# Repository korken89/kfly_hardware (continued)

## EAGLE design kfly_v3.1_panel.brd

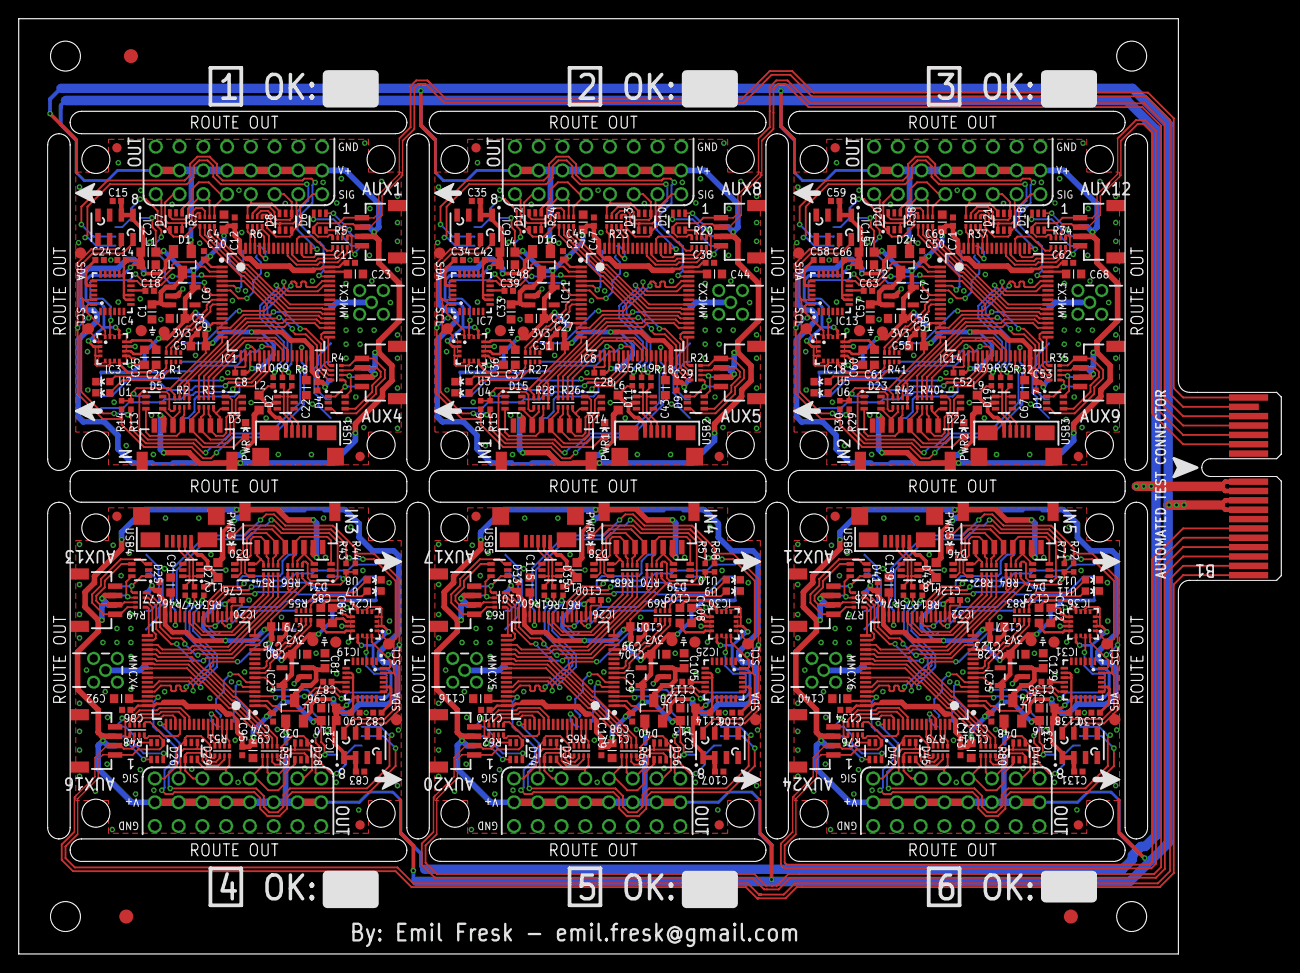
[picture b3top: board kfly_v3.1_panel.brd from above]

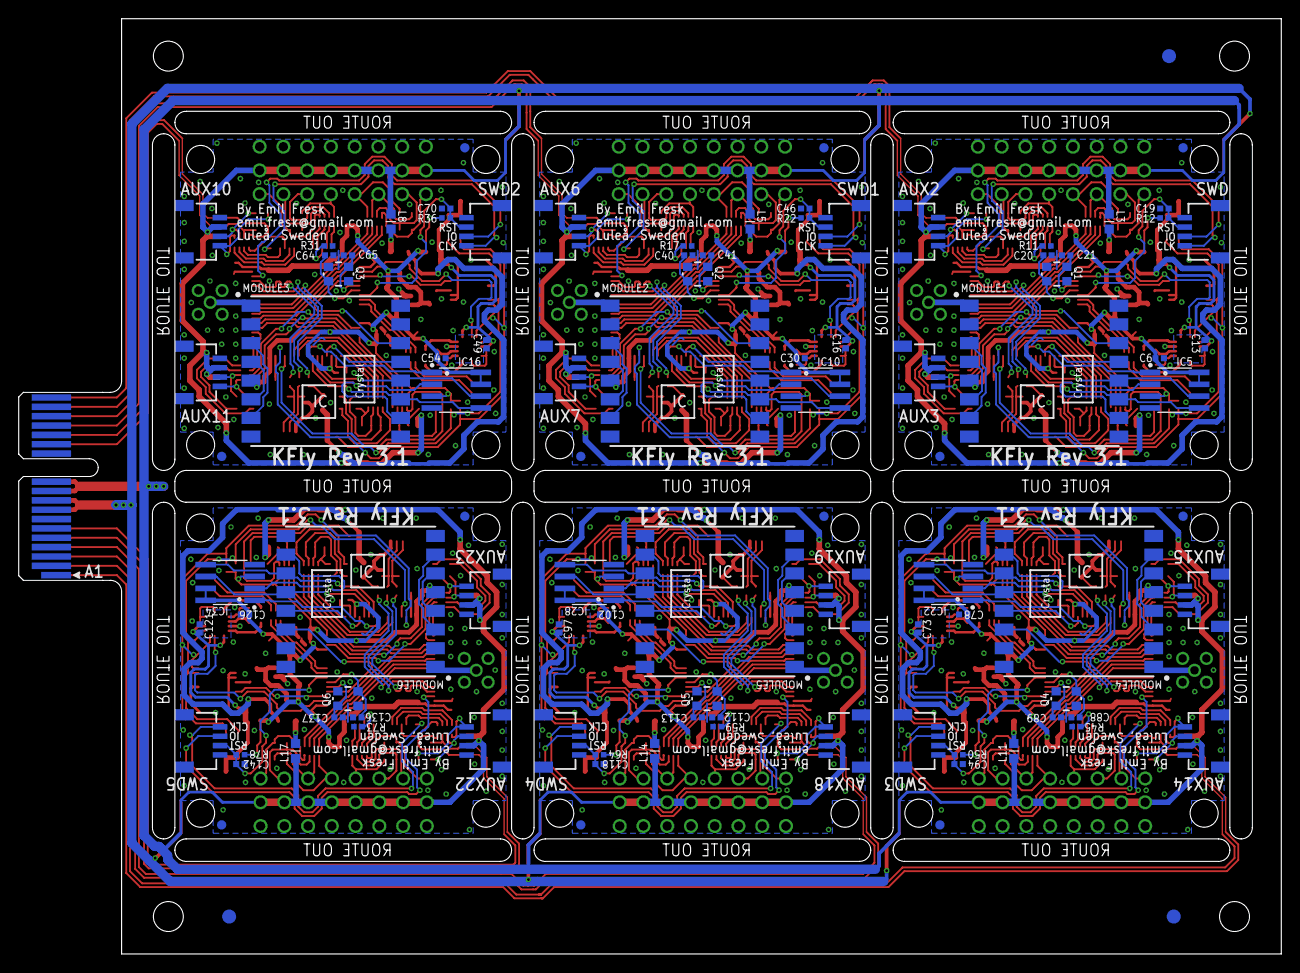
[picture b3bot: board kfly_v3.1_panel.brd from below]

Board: 4 copper layers, 135.0 x 100.0 mm, 511 parts (99 on the bottom side), 530 nets.

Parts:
AUX1, AUX2, AUX3, AUX4, AUX5, AUX6, AUX7, AUX8, AUX9, AUX10, AUX11, AUX12, AUX13, AUX14, AUX15, AUX16, AUX17, AUX18, AUX19, AUX20, AUX21, AUX22, AUX23, AUX24: JST-4PIN-SIDE-1.0; JST-4PIN-SIDE
C1, C2, C3, C4, C5, C31, C32, C33, C45, C48, C55, C56, C57, C69, C72, C79, C80, C81, C93, C96, C103, C104, C105, C117, C120, C127, C128, C129, C141, C144: 10u; CAPC1608X92N
C6, C7, C8, C9, C10, C11, C12, C13, C14, C15, C16, C17, C18, C19, C27, C28, C29, C30, C35, C38, C39, C42, C46, C47, C49, C50, C51, C52, C53, C54, C59, C62, C63, C66, C70, C71, C73, C74, C75, C76, C77, C78, C83, C86, C87, C90, C94, C95, C97, C98, C99, C100, C101, C102, C107, C110, C111, C114, C118, C119, C121, C122, C123, C124, C125, C126, C131, C134, C135, C138, C142, C143: 100n; CAPC1005X60N
C20, C21, C40, C41, C64, C65, C88, C89, C112, C113, C136, C137: 12p; CAPC1005X60N
C22, C23, C43, C44, C67, C68, C91, C92, C115, C116, C139, C140: 2.2u; CAPC1608X92N
C24, C34, C58, C82, C106, C130: 2.2n; CAPC1005X60N
C25, C36, C60, C84, C108, C132: 4.7u; CAPC1608X92N
C26, C37, C61, C85, C109, C133: 220n; CAPC1608X92N
D1, D16, D24, D32, D40, D48: BAT54C; SOT23
D2, D3, D4, D5, D6, D7, D8, D9, D10, D11, D12, D13, D14, D15, D17, D18, D19, D20, D21, D22, D23, D25, D26, D27, D28, D29, D30, D31, D33, D34, D35, D36, D37, D38, D39, D41, D42, D43, D44, D45, D46, D47: ESD5V3U4RRS; SOT363
E$1, E$2, E$3, E$4, E$5, E$6: FID1.5
E$7: PCI_2X18_PCB
ENGINE1, ENGINE2, ENGINE3, ENGINE4, ENGINE5, ENGINE6, ENGINE7, ENGINE8, ENGINE9, ENGINE10, ENGINE11, ENGINE12, ENGINE13, ENGINE14, ENGINE15, ENGINE16, ENGINE17, ENGINE18, ENGINE19, ENGINE20, ENGINE21, ENGINE22, ENGINE23, ENGINE24, ENGINE25, ENGINE26, ENGINE27, ENGINE28, ENGINE29, ENGINE30, ENGINE31, ENGINE32, ENGINE33, ENGINE34, ENGINE35, ENGINE36, ENGINE37, ENGINE38, ENGINE39, ENGINE40, ENGINE41, ENGINE42, ENGINE43, ENGINE44, ENGINE45, ENGINE46, ENGINE47, ENGINE48: M03_90DEG
FID1, FID2, FID3, FID4, FID5, FID6, FID7, FID8, FID9, FID10, FID11, FID12, FID13, FID14, FID15, FID16, FID17, FID18, FID19, FID20, FID21, FID22, FID23, FID24: FIDUTIALS1.0; FID1.0
IC1, IC8, IC14, IC20, IC26, IC32: STM32F405RX; LQFP64-10X10
IC2, IC9, IC15, IC21, IC27, IC33: MS5611-01BA03; MS5611
IC3, IC12, IC18, IC24, IC30, IC36: HMC5983; LPCC16
IC4, IC7, IC13, IC19, IC25, IC31: MPU-6050; QFN-24
IC5, IC10, IC16, IC22, IC28, IC34: SPI_FLASH-X25XXSMD; SO08
IC6, IC11, IC17, IC23, IC29, IC35: MCP1824; SOT23-5
IN, IN1, IN2, IN3, IN4, IN5: JST-8PIN-SIDE-1.0; JST-8PIN-SIDE
L1, L2, L3, L4, L5, L6, L7, L8, L9, L10, L11, L12, L13, L14, L15, L16, L17, L18: INDC1608X95N
MMCX1, MMCX2, MMCX3, MMCX4, MMCX5, MMCX6: MMCX_THROUGHHOLE_RIGHTANGLE
MODULE1, MODULE2, MODULE3, MODULE4, MODULE5, MODULE6: RFM22SMD; RFM22-XXX-S2
PWR, PWR1, PWR2, PWR3, PWR4, PWR5: LED-0603
Q1, Q2, Q3, Q4, Q5, Q6: 2.5X3.2CRYSTAL
R1, R2, R3, R4, R5, R6, R7, R20, R21, R23, R24, R26, R27, R28, R34, R35, R37, R38, R40, R41, R42, R48, R49, R51, R52, R54, R55, R56, R62, R63, R65, R66, R68, R69, R70, R76, R77, R79, R80, R82, R83, R84: RESISTORARRAY_0804
R8, R9, R18, R19, R32, R33, R46, R47, R60, R61, R74, R75: 22; RESC1005X40AN
R10, R11, R12, R17, R22, R25, R31, R36, R39, R45, R50, R53, R59, R64, R67, R73, R78, R81: 10k; RESC1005X40AN
R13, R14, R15, R16, R29, R30, R43, R44, R57, R58, R71, R72: 2.2k; RESC1005X40AN
SWD, SWD1, SWD2, SWD3, SWD4, SWD5: JST-4PIN-SIDE-1.0; JST-4PIN-SIDE
TEST1, TEST2, TEST3, TEST4, TEST5, TEST6, TEST7, TEST8, TEST9, TEST10, TEST11, TEST12, TEST13, TEST14, TEST15, TEST16, TEST17, TEST18, TEST19, TEST20, TEST21, TEST22, TEST23, TEST24: TESTPOINT_1.2
U1, U2, U3, U4, U5, U6, U7, U8, U9, U10, U11, U12: LED-0603
USB1, USB2, USB3, USB4, USB5, USB6: USB-MICRO-B-BOTTOM; MICROUSB_TYPEB_SURFACE

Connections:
!SRST: C19.1, IC1.7, R12.2, SWD.3
!SRST1: C46.1, IC8.7, R22.2, SWD1.3
!SRST2: C70.1, IC14.7, R36.2, SWD2.3
!SRST3: C94.1, IC20.7, R50.2, SWD3.3
!SRST4: C118.1, IC26.7, R64.2, SWD4.3
!SRST5: C142.1, IC32.7, R78.2, SWD5.3
+3V1: C17.1, C27.1, C28.1, C29.1, C30.1, C31.1, C32.1, C38.1, C45.1, C47.1, IC8.1, IC8.13, IC8.19, IC8.32, IC8.48, IC8.64, IC10.3, IC10.7, IC10.8, IC11.5, L4.1, MODULE2.5, R15.1, R16.1, R22.1, R28.4, TEST7.1
+3V2: C50.1, C51.1, C52.1, C53.1, C54.1, C55.1, C56.1, C62.1, C69.1, C71.1, IC14.1, IC14.13, IC14.19, IC14.32, IC14.48, IC14.64, IC16.3, IC16.7, IC16.8, IC17.5, L7.1, MODULE3.5, R29.1, R30.1, R36.1, R42.4, TEST11.1
+3V3: C3.1, C4.1, C5.1, C6.1, C7.1, C8.1, C9.1, C10.1, C11.1, C12.1, IC1.1, IC1.13, IC1.19, IC1.32, IC1.48, IC1.64, IC5.3, IC5.7, IC5.8, IC6.5, L1.1, MODULE1.5, R2.4, R12.1, R13.1, R14.1, TEST3.1
+3V4: C74.1, C75.1, C76.1, C77.1, C78.1, C79.1, C80.1, C86.1, C93.1, C95.1, IC20.1, IC20.13, IC20.19, IC20.32, IC20.48, IC20.64, IC22.3, IC22.7, IC22.8, IC23.5, L10.1, MODULE4.5, R43.1, R44.1, R50.1, R56.4, TEST15.1
+3V5: C98.1, C99.1, C100.1, C101.1, C102.1, C103.1, C104.1, C110.1, C117.1, C119.1, IC26.1, IC26.13, IC26.19, IC26.32, IC26.48, IC26.64, IC28.3, IC28.7, IC28.8, IC29.5, L13.1, MODULE5.5, R57.1, R58.1, R64.1, R70.4, TEST19.1
+3V6: C122.1, C123.1, C124.1, C125.1, C126.1, C127.1, C128.1, C134.1, C141.1, C143.1, IC32.1, IC32.13, IC32.19, IC32.32, IC32.48, IC32.64, IC34.3, IC34.7, IC34.8, IC35.5, L16.1, MODULE6.5, R71.1, R72.1, R78.1, R84.4, TEST23.1
+5V: AUX1.2, AUX2.2, AUX3.2, AUX4.2, ENGINE1.2, ENGINE2.2, ENGINE3.2, ENGINE4.2, ENGINE5.2, ENGINE6.2, ENGINE7.2, ENGINE8.2, IN.2, IN.NC2, L3.1
+5V1: AUX5.2, AUX6.2, AUX7.2, AUX8.2, ENGINE9.2, ENGINE10.2, ENGINE11.2, ENGINE12.2, ENGINE13.2, ENGINE14.2, ENGINE15.2, ENGINE16.2, IN1.2, IN1.NC2, L5.1
+5V2: AUX9.2, AUX10.2, AUX11.2, AUX12.2, ENGINE17.2, ENGINE18.2, ENGINE19.2, ENGINE20.2, ENGINE21.2, ENGINE22.2, ENGINE23.2, ENGINE24.2, IN2.2, IN2.NC2, L8.1
+5V3: AUX13.2, AUX14.2, AUX15.2, AUX16.2, ENGINE25.2, ENGINE26.2, ENGINE27.2, ENGINE28.2, ENGINE29.2, ENGINE30.2, ENGINE31.2, ENGINE32.2, IN3.2, IN3.NC2, L11.1
+5V4: AUX17.2, AUX18.2, AUX19.2, AUX20.2, ENGINE33.2, ENGINE34.2, ENGINE35.2, ENGINE36.2, ENGINE37.2, ENGINE38.2, ENGINE39.2, ENGINE40.2, IN4.2, IN4.NC2, L14.1
+5V5: AUX21.2, AUX22.2, AUX23.2, AUX24.2, ENGINE41.2, ENGINE42.2, ENGINE43.2, ENGINE44.2, ENGINE45.2, ENGINE46.2, ENGINE47.2, ENGINE48.2, IN5.2, IN5.NC2, L17.1
CAN_RX: IC1.33, R4.5
CAN_RX1: IC8.33, R21.5
CAN_RX2: IC14.33, R35.5
CAN_RX3: IC20.33, R49.5
CAN_RX4: IC26.33, R63.5
CAN_RX5: IC32.33, R77.5
CAN_TX: IC1.34, R4.6
CAN_TX1: IC8.34, R21.6
CAN_TX2: IC14.34, R35.6
CAN_TX3: IC20.34, R49.6
CAN_TX4: IC26.34, R63.6
CAN_TX5: IC32.34, R77.6
CONTROLL1_IN: IC1.26, R3.2
CONTROLL1_IN1: IC8.26, R26.2
CONTROLL1_IN2: IC14.26, R40.2
CONTROLL1_IN3: IC20.26, R54.2
CONTROLL1_IN4: IC26.26, R68.2
CONTROLL1_IN5: IC32.26, R82.2
CONTROLL2_IN: IC1.27, R3.3
CONTROLL2_IN1: IC8.27, R26.3
CONTROLL2_IN2: IC14.27, R40.3
CONTROLL2_IN3: IC20.27, R54.3
CONTROLL2_IN4: IC26.27, R68.3
CONTROLL2_IN5: IC32.27, R82.3
CONTROLL3_IN: IC1.35, R3.4
CONTROLL3_IN1: IC8.35, R26.4
CONTROLL3_IN2: IC14.35, R40.4
CONTROLL3_IN3: IC20.35, R54.4
CONTROLL3_IN4: IC26.35, R68.4
CONTROLL3_IN5: IC32.35, R82.4
CONTROLL4_IN: IC1.36, R2.1, R2.2, R2.8
CONTROLL4_IN1: IC8.36, R28.1, R28.2, R28.8
CONTROLL4_IN2: IC14.36, R42.1, R42.2, R42.8
CONTROLL4_IN3: IC20.36, R56.1, R56.2, R56.8
CONTROLL4_IN4: IC26.36, R70.1, R70.2, R70.8
CONTROLL4_IN5: IC32.36, R84.1, R84.2, R84.8
CONTROLL5_IN: IC1.16, R2.3
CONTROLL5_IN1: IC8.16, R28.3
CONTROLL5_IN2: IC14.16, R42.3
CONTROLL5_IN3: IC20.16, R56.3
CONTROLL5_IN4: IC26.16, R70.3
CONTROLL5_IN5: IC32.16, R84.3
CONTROLL6_IN: IC1.17, R3.1
CONTROLL6_IN1: IC8.17, R26.1
CONTROLL6_IN2: IC14.17, R40.1
CONTROLL6_IN3: IC20.17, R54.1
CONTROLL6_IN4: IC26.17, R68.1
CONTROLL6_IN5: IC32.17, R82.1
D_N: IC1.44, R9.1
D_N1: IC8.44, R19.1
D_N2: IC14.44, R33.1
D_N3: IC20.44, R47.1
D_N4: IC26.44, R61.1
D_N5: IC32.44, R75.1
D_P: IC1.45, R8.1
D_P1: IC8.45, R18.1
D_P2: IC14.45, R32.1
D_P3: IC20.45, R46.1
D_P4: IC26.45, R60.1
D_P5: IC32.45, R74.1
ENGINE1_PWM: IC1.62, R6.1
ENGINE1_PWM1: IC8.62, R23.1
ENGINE1_PWM2: IC14.62, R37.1
ENGINE1_PWM3: IC20.62, R51.1
ENGINE1_PWM4: IC26.62, R65.1
ENGINE1_PWM5: IC32.62, R79.1
ENGINE2_PWM: IC1.61, R6.2
ENGINE2_PWM1: IC8.61, R23.2
ENGINE2_PWM2: IC14.61, R37.2
ENGINE2_PWM3: IC20.61, R51.2
ENGINE2_PWM4: IC26.61, R65.2
ENGINE2_PWM5: IC32.61, R79.2
ENGINE3_PWM: IC1.59, R6.3
ENGINE3_PWM1: IC8.59, R23.3
ENGINE3_PWM2: IC14.59, R37.3
ENGINE3_PWM3: IC20.59, R51.3
ENGINE3_PWM4: IC26.59, R65.3
ENGINE3_PWM5: IC32.59, R79.3
ENGINE4_PWM: IC1.58, R6.4
ENGINE4_PWM1: IC8.58, R23.4
ENGINE4_PWM2: IC14.58, R37.4
ENGINE4_PWM3: IC20.58, R51.4
ENGINE4_PWM4: IC26.58, R65.4
ENGINE4_PWM5: IC32.58, R79.4
ENGINE5_PWM: IC1.40, R7.4
ENGINE5_PWM1: IC8.40, R24.4
ENGINE5_PWM2: IC14.40, R38.4
ENGINE5_PWM3: IC20.40, R52.4
ENGINE5_PWM4: IC26.40, R66.4
ENGINE5_PWM5: IC32.40, R80.4
ENGINE6_PWM: IC1.39, R7.3
ENGINE6_PWM1: IC8.39, R24.3
ENGINE6_PWM2: IC14.39, R38.3
ENGINE6_PWM3: IC20.39, R52.3
ENGINE6_PWM4: IC26.39, R66.3
ENGINE6_PWM5: IC32.39, R80.3
ENGINE7_PWM: IC1.38, R7.2
ENGINE7_PWM1: IC8.38, R24.2
ENGINE7_PWM2: IC14.38, R38.2
ENGINE7_PWM3: IC20.38, R52.2
ENGINE7_PWM4: IC26.38, R66.2
ENGINE7_PWM5: IC32.38, R80.2
ENGINE8_PWM: IC1.37, R7.1
ENGINE8_PWM1: IC8.37, R24.1
ENGINE8_PWM2: IC14.37, R38.1
ENGINE8_PWM3: IC20.37, R52.1
ENGINE8_PWM4: IC26.37, R66.1
ENGINE8_PWM5: IC32.37, R80.1
FLASH_SEL: IC1.24, IC5.1
FLASH_SEL1: IC8.24, IC10.1
FLASH_SEL2: IC14.24, IC16.1
FLASH_SEL3: IC20.24, IC22.1
FLASH_SEL4: IC26.24, IC28.1
FLASH_SEL5: IC32.24, IC34.1
GND: AUX1.1, AUX1.NC1, AUX1.NC2, AUX2.1, AUX2.NC1, AUX2.NC2, AUX3.1, AUX3.NC1, AUX3.NC2, AUX4.1, AUX4.NC1, AUX4.NC2, C1.2, C2.2, C3.2, C4.2, C5.2, C6.2, C7.2, C8.2, C9.2, C10.2, C11.2, C12.2, C13.2, C14.2, C15.2, C18.2, C19.2, C20.1, C21.1, C22.2, C23.2, C24.2, C25.2, D2.5, D3.5, D4.5, D5.5, D6.5, D7.5, D8.5, ENGINE1.1, ENGINE2.1, ENGINE3.1, ENGINE4.1, ENGINE5.1, ENGINE6.1, ENGINE7.1, ENGINE8.1, IC1.12, IC1.18, IC1.63, IC2.3, IC2.4, IC2.5, IC3.9, IC3.11, IC4.18, IC5.4, IC6.2, IN.1, IN.NC1, MMCX1.G1, MMCX1.G2, MMCX1.G3, MMCX1.G4, MODULE1.2, MODULE1.9, MODULE1.15, MODULE1.16, PWR.C, R1.1, R1.2, R1.7, R1.8, R11.1, SWD.4, SWD.NC1, SWD.NC2, TEST4.1, U1.C, U2.C, USB1.5, USB1.MNT1, USB1.MNT2, USB1.MNT3, USB1.MNT4
GND1: AUX5.1, AUX5.NC1, AUX5.NC2, AUX6.1, AUX6.NC1, AUX6.NC2, AUX7.1, AUX7.NC1, AUX7.NC2, AUX8.1, AUX8.NC1, AUX8.NC2, C16.2, C17.2, C27.2, C28.2, C29.2, C30.2, C31.2, C32.2, C33.2, C34.2, C35.2, C36.2, C38.2, C39.2, C40.1, C41.1, C42.2, C43.2, C44.2, C45.2, C46.2, C47.2, C48.2, D9.5, D10.5, D11.5, D12.5, D13.5, D14.5, D15.5, ENGINE9.1, ENGINE10.1, ENGINE11.1, ENGINE12.1, ENGINE13.1, ENGINE14.1, ENGINE15.1, ENGINE16.1, IC7.18, IC8.12, IC8.18, IC8.63, IC9.3, IC9.4, IC9.5, IC10.4, IC11.2, IC12.9, IC12.11, IN1.1, IN1.NC1, MMCX2.G1, MMCX2.G2, MMCX2.G3, MMCX2.G4, MODULE2.2, MODULE2.9, MODULE2.15, MODULE2.16, PWR1.C, R17.1, R27.1, R27.2, R27.7, R27.8, SWD1.4, SWD1.NC1, SWD1.NC2, TEST8.1, U3.C, U4.C, USB2.5, USB2.MNT1, USB2.MNT2, USB2.MNT3, USB2.MNT4
GND2: AUX9.1, AUX9.NC1, AUX9.NC2, AUX10.1, AUX10.NC1, AUX10.NC2, AUX11.1, AUX11.NC1, AUX11.NC2, AUX12.1, AUX12.NC1, AUX12.NC2, C49.2, C50.2, C51.2, C52.2, C53.2, C54.2, C55.2, C56.2, C57.2, C58.2, C59.2, C60.2, C62.2, C63.2, C64.1, C65.1, C66.2, C67.2, C68.2, C69.2, C70.2, C71.2, C72.2, D17.5, D18.5, D19.5, D20.5, D21.5, D22.5, D23.5, ENGINE17.1, ENGINE18.1, ENGINE19.1, ENGINE20.1, ENGINE21.1, ENGINE22.1, ENGINE23.1, ENGINE24.1, IC13.18, IC14.12, IC14.18, IC14.63, IC15.3, IC15.4, IC15.5, IC16.4, IC17.2, IC18.9, IC18.11, IN2.1, IN2.NC1, MMCX3.G1, MMCX3.G2, MMCX3.G3, MMCX3.G4, MODULE3.2, MODULE3.9, MODULE3.15, MODULE3.16, PWR2.C, R31.1, R41.1, R41.2, R41.7, R41.8, SWD2.4, SWD2.NC1, SWD2.NC2, TEST12.1, U5.C, U6.C, USB3.5, USB3.MNT1, USB3.MNT2, USB3.MNT3, USB3.MNT4
GND3: AUX13.1, AUX13.NC1, AUX13.NC2, AUX14.1, AUX14.NC1, AUX14.NC2, AUX15.1, AUX15.NC1, AUX15.NC2, AUX16.1, AUX16.NC1, AUX16.NC2, C73.2, C74.2, C75.2, C76.2, C77.2, C78.2, C79.2, C80.2, C81.2, C82.2, C83.2, C84.2, C86.2, C87.2, C88.1, C89.1, C90.2, C91.2, C92.2, C93.2, C94.2, C95.2, C96.2, D25.5, D26.5, D27.5, D28.5, D29.5, D30.5, D31.5, ENGINE25.1, ENGINE26.1, ENGINE27.1, ENGINE28.1, ENGINE29.1, ENGINE30.1, ENGINE31.1, ENGINE32.1, IC19.18, IC20.12, IC20.18, IC20.63, IC21.3, IC21.4, IC21.5, IC22.4, IC23.2, IC24.9, IC24.11, IN3.1, IN3.NC1, MMCX4.G1, MMCX4.G2, MMCX4.G3, MMCX4.G4, MODULE4.2, MODULE4.9, MODULE4.15, MODULE4.16, PWR3.C, R45.1, R55.1, R55.2, R55.7, R55.8, SWD3.4, SWD3.NC1, SWD3.NC2, TEST16.1, U7.C, U8.C, USB4.5, USB4.MNT1, USB4.MNT2, USB4.MNT3, USB4.MNT4
GND4: AUX17.1, AUX17.NC1, AUX17.NC2, AUX18.1, AUX18.NC1, AUX18.NC2, AUX19.1, AUX19.NC1, AUX19.NC2, AUX20.1, AUX20.NC1, AUX20.NC2, C97.2, C98.2, C99.2, C100.2, C101.2, C102.2, C103.2, C104.2, C105.2, C106.2, C107.2, C108.2, C110.2, C111.2, C112.1, C113.1, C114.2, C115.2, C116.2, C117.2, C118.2, C119.2, C120.2, D33.5, D34.5, D35.5, D36.5, D37.5, D38.5, D39.5, ENGINE33.1, ENGINE34.1, ENGINE35.1, ENGINE36.1, ENGINE37.1, ENGINE38.1, ENGINE39.1, ENGINE40.1, IC25.18, IC26.12, IC26.18, IC26.63, IC27.3, IC27.4, IC27.5, IC28.4, IC29.2, IC30.9, IC30.11, IN4.1, IN4.NC1, MMCX5.G1, MMCX5.G2, MMCX5.G3, MMCX5.G4, MODULE5.2, MODULE5.9, MODULE5.15, MODULE5.16, PWR4.C, R59.1, R69.1, R69.2, R69.7, R69.8, SWD4.4, SWD4.NC1, SWD4.NC2, TEST20.1, U9.C, U10.C, USB5.5, USB5.MNT1, USB5.MNT2, USB5.MNT3, USB5.MNT4
GND5: AUX21.1, AUX21.NC1, AUX21.NC2, AUX22.1, AUX22.NC1, AUX22.NC2, AUX23.1, AUX23.NC1, AUX23.NC2, AUX24.1, AUX24.NC1, AUX24.NC2, C121.2, C122.2, C123.2, C124.2, C125.2, C126.2, C127.2, C128.2, C129.2, C130.2, C131.2, C132.2, C134.2, C135.2, C136.1, C137.1, C138.2, C139.2, C140.2, C141.2, C142.2, C143.2, C144.2, D41.5, D42.5, D43.5, D44.5, D45.5, D46.5, D47.5, ENGINE41.1, ENGINE42.1, ENGINE43.1, ENGINE44.1, ENGINE45.1, ENGINE46.1, ENGINE47.1, ENGINE48.1, IC31.18, IC32.12, IC32.18, IC32.63, IC33.3, IC33.4, IC33.5, IC34.4, IC35.2, IC36.9, IC36.11, IN5.1, IN5.NC1, MMCX6.G1, MMCX6.G2, MMCX6.G3, MMCX6.G4, MODULE6.2, MODULE6.9, MODULE6.15, MODULE6.16, PWR5.C, R73.1, R83.1, R83.2, R83.7, R83.8, SWD5.4, SWD5.NC1, SWD5.NC2, TEST24.1, U11.C, U12.C, USB6.5, USB6.MNT1, USB6.MNT2, USB6.MNT3, USB6.MNT4
GND_PANEL: E$7.B8, E$7.B9
MAG_INT: IC1.2, IC3.15
MAG_INT1: IC8.2, IC12.15
MAG_INT2: IC14.2, IC18.15
MAG_INT3: IC20.2, IC24.15
MAG_INT4: IC26.2, IC30.15
MAG_INT5: IC32.2, IC36.15
MPU_INT: IC1.3, IC4.12
MPU_INT1: IC7.12, IC8.3
MPU_INT2: IC13.12, IC14.3
MPU_INT3: IC19.12, IC20.3
MPU_INT4: IC25.12, IC26.3
MPU_INT5: IC31.12, IC32.3
unnamed: C25.1, IC3.10
unnamed: D2.6, R8.2, USB1.3
unnamed: D7.1, ENGINE8.3, R7.8
unnamed: D7.3, ENGINE7.3, R7.7
unnamed: D7.6, ENGINE6.3, R7.6
unnamed: AUX2.3, D6.4, R5.2
unnamed: D2.1, R9.2, USB1.2
unnamed: C26.1, IC3.8
unnamed: PWR.A, R2.5
unnamed: C26.2, IC3.12
unnamed: R1.5, U2.A
unnamed: D7.4, ENGINE5.3, R7.5
unnamed: C18.1, IC4.10
unnamed: C24.1, IC4.20
unnamed: AUX3.3, D4.6, R4.2
unnamed: D8.1, ENGINE2.3, R6.6
unnamed: D8.3, ENGINE1.3, R6.5
unnamed: R1.6, U1.A
unnamed: IC1.60, R11.2
unnamed: IC1.8, R1.4
unnamed: D1.2, L2.2
unnamed: D8.6, ENGINE4.3, R6.8
unnamed: D5.4, IN.3, R2.6
unnamed: IC1.9, R1.3
unnamed: C20.2, IC1.6, Q1.1
unnamed: C21.2, IC1.5, Q1.3
unnamed: D3.3, IN.8, R3.8
unnamed: D3.4, IN.5, R3.5
unnamed: D8.4, ENGINE3.3, R6.7
unnamed: AUX4.4, D4.3, R4.4
unnamed: AUX4.3, D4.4, R4.3
unnamed: AUX3.4, D4.1, R4.1
unnamed: D3.1, IN.7, R3.7
unnamed: D3.6, IN.6, R3.6
unnamed: IC1.42, R10.1
unnamed: C43.1, IC8.31
unnamed: C44.1, IC8.47
unnamed: AUX1.3, D6.3, R5.3
unnamed: IC8.60, R17.2
unnamed: AUX2.4, D6.6, R5.1
unnamed: IC8.42, R25.1
unnamed: PWR1.A, R28.5
unnamed: R27.6, U4.A
unnamed: C22.1, IC1.31
unnamed: D1.1, L3.2
unnamed: D5.3, IN.4, R2.7
unnamed: IC8.8, R27.4
unnamed: IC8.9, R27.3
unnamed: D16.1, L5.2
unnamed: C23.1, IC1.47
unnamed: AUX1.4, D6.1, R5.4
unnamed: D16.2, L6.2
unnamed: C36.1, IC12.10
unnamed: C37.1, IC12.8
unnamed: C37.2, IC12.12
unnamed: MMCX1.S, MODULE1.1
unnamed: C39.1, IC7.10
unnamed: C34.1, IC7.20
unnamed: D11.6, R18.2, USB2.3
unnamed: D11.1, R19.2, USB2.2
unnamed: AUX6.4, D10.6, R20.1
unnamed: AUX8.4, D10.1, R20.4
unnamed: D15.3, IN1.4, R28.7
unnamed: D15.4, IN1.3, R28.6
unnamed: D12.3, ENGINE15.3, R24.7
unnamed: D12.6, ENGINE14.3, R24.6
unnamed: MODULE1.4, MODULE1.6
unnamed: MODULE1.3, MODULE1.7
unnamed: D13.1, ENGINE10.3, R23.6
unnamed: D13.3, ENGINE9.3, R23.5
unnamed: MMCX2.S, MODULE2.1
unnamed: MODULE2.4, MODULE2.6
unnamed: MODULE2.3, MODULE2.7
unnamed: C40.2, IC8.6, Q2.1
unnamed: C41.2, IC8.5, Q2.3
unnamed: D14.3, IN1.8, R26.8
unnamed: D14.4, IN1.5, R26.5
unnamed: D13.6, ENGINE12.3, R23.8
unnamed: D13.4, ENGINE11.3, R23.7
unnamed: D12.4, ENGINE13.3, R24.5
unnamed: D12.1, ENGINE16.3, R24.8
unnamed: AUX6.3, D10.4, R20.2
unnamed: AUX5.4, D9.3, R21.4
unnamed: AUX5.3, D9.4, R21.3
unnamed: R27.5, U3.A
unnamed: AUX7.3, D9.6, R21.2
unnamed: AUX7.4, D9.1, R21.1
unnamed: D14.1, IN1.7, R26.7
unnamed: D14.6, IN1.6, R26.6
unnamed: AUX8.3, D10.3, R20.3
unnamed: C67.1, IC14.31
unnamed: C68.1, IC14.47
unnamed: IC14.60, R31.2
unnamed: IC14.42, R39.1
unnamed: PWR2.A, R42.5
unnamed: R41.6, U6.A
unnamed: IC14.8, R41.4
unnamed: IC14.9, R41.3
unnamed: D24.1, L8.2
unnamed: D24.2, L9.2
unnamed: C60.1, IC18.10
unnamed: C61.1, IC18.8
unnamed: C61.2, IC18.12
unnamed: C63.1, IC13.10
unnamed: C58.1, IC13.20
unnamed: D19.6, R32.2, USB3.3
unnamed: D19.1, R33.2, USB3.2
unnamed: AUX10.4, D18.6, R34.1
unnamed: AUX12.4, D18.1, R34.4
unnamed: D23.3, IN2.4, R42.7
unnamed: D23.4, IN2.3, R42.6
unnamed: D20.3, ENGINE23.3, R38.7
unnamed: D20.6, ENGINE22.3, R38.6
unnamed: D21.1, ENGINE18.3, R37.6
unnamed: D21.3, ENGINE17.3, R37.5
unnamed: MMCX3.S, MODULE3.1
unnamed: MODULE3.4, MODULE3.6
unnamed: MODULE3.3, MODULE3.7
unnamed: C64.2, IC14.6, Q3.1
unnamed: C65.2, IC14.5, Q3.3
unnamed: D22.3, IN2.8, R40.8
unnamed: D22.4, IN2.5, R40.5
unnamed: D21.6, ENGINE20.3, R37.8
unnamed: D21.4, ENGINE19.3, R37.7
unnamed: D20.4, ENGINE21.3, R38.5
unnamed: D20.1, ENGINE24.3, R38.8
unnamed: AUX10.3, D18.4, R34.2
unnamed: AUX9.4, D17.3, R35.4
unnamed: AUX9.3, D17.4, R35.3
unnamed: R41.5, U5.A
unnamed: AUX11.3, D17.6, R35.2
unnamed: AUX11.4, D17.1, R35.1
unnamed: D22.1, IN2.7, R40.7
unnamed: D22.6, IN2.6, R40.6
unnamed: AUX12.3, D18.3, R34.3
unnamed: C91.1, IC20.31
unnamed: C92.1, IC20.47
unnamed: IC20.60, R45.2
unnamed: IC20.42, R53.1
unnamed: PWR3.A, R56.5
unnamed: R55.6, U8.A
unnamed: IC20.8, R55.4
unnamed: IC20.9, R55.3
unnamed: D32.1, L11.2
unnamed: D32.2, L12.2
unnamed: C84.1, IC24.10
unnamed: C85.1, IC24.8
unnamed: C85.2, IC24.12
unnamed: C87.1, IC19.10
unnamed: C82.1, IC19.20
unnamed: D27.6, R46.2, USB4.3
unnamed: D27.1, R47.2, USB4.2
unnamed: AUX14.4, D26.6, R48.1
unnamed: AUX16.4, D26.1, R48.4
unnamed: D31.3, IN3.4, R56.7
unnamed: D31.4, IN3.3, R56.6
unnamed: D28.3, ENGINE31.3, R52.7
unnamed: D28.6, ENGINE30.3, R52.6
unnamed: D29.1, ENGINE26.3, R51.6
unnamed: D29.3, ENGINE25.3, R51.5
unnamed: MMCX4.S, MODULE4.1
unnamed: MODULE4.4, MODULE4.6
unnamed: MODULE4.3, MODULE4.7
unnamed: C88.2, IC20.6, Q4.1
unnamed: C89.2, IC20.5, Q4.3
unnamed: D30.3, IN3.8, R54.8
unnamed: D30.4, IN3.5, R54.5
unnamed: D29.6, ENGINE28.3, R51.8
unnamed: D29.4, ENGINE27.3, R51.7
unnamed: D28.4, ENGINE29.3, R52.5
unnamed: D28.1, ENGINE32.3, R52.8
unnamed: AUX14.3, D26.4, R48.2
unnamed: AUX13.4, D25.3, R49.4
unnamed: AUX13.3, D25.4, R49.3
unnamed: R55.5, U7.A
unnamed: AUX15.3, D25.6, R49.2
unnamed: AUX15.4, D25.1, R49.1
unnamed: D30.1, IN3.7, R54.7
unnamed: D30.6, IN3.6, R54.6
unnamed: AUX16.3, D26.3, R48.3
unnamed: C115.1, IC26.31
unnamed: C116.1, IC26.47
unnamed: IC26.60, R59.2
unnamed: IC26.42, R67.1
unnamed: PWR4.A, R70.5
unnamed: R69.6, U10.A
unnamed: IC26.8, R69.4
unnamed: IC26.9, R69.3
unnamed: D40.1, L14.2
unnamed: D40.2, L15.2
unnamed: C108.1, IC30.10
unnamed: C109.1, IC30.8
unnamed: C109.2, IC30.12
unnamed: C111.1, IC25.10
unnamed: C106.1, IC25.20
unnamed: D35.6, R60.2, USB5.3
unnamed: D35.1, R61.2, USB5.2
unnamed: AUX18.4, D34.6, R62.1
unnamed: AUX20.4, D34.1, R62.4
unnamed: D39.3, IN4.4, R70.7
unnamed: D39.4, IN4.3, R70.6
unnamed: D36.3, ENGINE39.3, R66.7
unnamed: D36.6, ENGINE38.3, R66.6
unnamed: D37.1, ENGINE34.3, R65.6
unnamed: D37.3, ENGINE33.3, R65.5
unnamed: MMCX5.S, MODULE5.1
unnamed: MODULE5.4, MODULE5.6
unnamed: MODULE5.3, MODULE5.7
unnamed: C112.2, IC26.6, Q5.1
unnamed: C113.2, IC26.5, Q5.3
unnamed: D38.3, IN4.8, R68.8
unnamed: D38.4, IN4.5, R68.5
unnamed: D37.6, ENGINE36.3, R65.8
unnamed: D37.4, ENGINE35.3, R65.7
unnamed: D36.4, ENGINE37.3, R66.5
unnamed: D36.1, ENGINE40.3, R66.8
unnamed: AUX18.3, D34.4, R62.2
unnamed: AUX17.4, D33.3, R63.4
unnamed: AUX17.3, D33.4, R63.3
unnamed: R69.5, U9.A
unnamed: AUX19.3, D33.6, R63.2
unnamed: AUX19.4, D33.1, R63.1
unnamed: D38.1, IN4.7, R68.7
unnamed: D38.6, IN4.6, R68.6
unnamed: AUX20.3, D34.3, R62.3
unnamed: C139.1, IC32.31
unnamed: C140.1, IC32.47
unnamed: IC32.60, R73.2
unnamed: IC32.42, R81.1
unnamed: PWR5.A, R84.5
unnamed: R83.6, U12.A
unnamed: IC32.8, R83.4
unnamed: IC32.9, R83.3
unnamed: D48.1, L17.2
unnamed: D48.2, L18.2
unnamed: C132.1, IC36.10
unnamed: C133.1, IC36.8
unnamed: C133.2, IC36.12
unnamed: C135.1, IC31.10
unnamed: C130.1, IC31.20
unnamed: D43.6, R74.2, USB6.3
unnamed: D43.1, R75.2, USB6.2
unnamed: AUX22.4, D42.6, R76.1
unnamed: AUX24.4, D42.1, R76.4
unnamed: D47.3, IN5.4, R84.7
unnamed: D47.4, IN5.3, R84.6
unnamed: D44.3, ENGINE47.3, R80.7
unnamed: D44.6, ENGINE46.3, R80.6
unnamed: D45.1, ENGINE42.3, R79.6
unnamed: D45.3, ENGINE41.3, R79.5
unnamed: MMCX6.S, MODULE6.1
unnamed: MODULE6.4, MODULE6.6
unnamed: MODULE6.3, MODULE6.7
unnamed: C136.2, IC32.6, Q6.1
unnamed: C137.2, IC32.5, Q6.3
unnamed: D46.3, IN5.8, R82.8
unnamed: D46.4, IN5.5, R82.5
unnamed: D45.6, ENGINE44.3, R79.8
unnamed: D45.4, ENGINE43.3, R79.7
unnamed: D44.4, ENGINE45.3, R80.5
unnamed: D44.1, ENGINE48.3, R80.8
unnamed: AUX22.3, D42.4, R76.2
unnamed: AUX21.4, D41.3, R77.4
unnamed: AUX21.3, D41.4, R77.3
unnamed: R83.5, U11.A
unnamed: AUX23.3, D41.6, R77.2
unnamed: AUX23.4, D41.1, R77.1
unnamed: D46.1, IN5.7, R82.7
unnamed: D46.6, IN5.6, R82.6
unnamed: AUX24.3, D42.3, R76.3
RF_IRQ: IC1.4, MODULE1.14
RF_IRQ1: IC8.4, MODULE2.14
RF_IRQ2: IC14.4, MODULE3.14
RF_IRQ3: IC20.4, MODULE4.14
RF_IRQ4: IC26.4, MODULE5.14
RF_IRQ5: IC32.4, MODULE6.14
RF_MISO: IC1.22, IC5.2, MODULE1.10
RF_MISO1: IC8.22, IC10.2, MODULE2.10
RF_MISO2: IC14.22, IC16.2, MODULE3.10
RF_MISO3: IC20.22, IC22.2, MODULE4.10
RF_MISO4: IC26.22, IC28.2, MODULE5.10
RF_MISO5: IC32.22, IC34.2, MODULE6.10
RF_MOSI: IC1.23, IC5.5, MODULE1.11
RF_MOSI1: IC8.23, IC10.5, MODULE2.11
RF_MOSI2: IC14.23, IC16.5, MODULE3.11
RF_MOSI3: IC20.23, IC22.5, MODULE4.11
RF_MOSI4: IC26.23, IC28.5, MODULE5.11
RF_MOSI5: IC32.23, IC34.5, MODULE6.11
RF_SCLK: IC1.21, IC5.6, MODULE1.12
RF_SCLK1: IC8.21, IC10.6, MODULE2.12
RF_SCLK2: IC14.21, IC16.6, MODULE3.12
RF_SCLK3: IC20.21, IC22.6, MODULE4.12
RF_SCLK4: IC26.21, IC28.6, MODULE5.12
RF_SCLK5: IC32.21, IC34.6, MODULE6.12
RF_SEL: IC1.20, MODULE1.13
RF_SEL1: IC8.20, MODULE2.13
RF_SEL2: IC14.20, MODULE3.13
RF_SEL3: IC20.20, MODULE4.13
RF_SEL4: IC26.20, MODULE5.13
RF_SEL5: IC32.20, MODULE6.13
RXD1: IC8.15, R21.8
RXD2: IC8.54, R20.8
RXD3: IC1.52, R5.5
RXD4: IC1.15, R4.8
RXD5: IC1.54, R5.8
RXD6: IC8.52, R20.5
RXD7: IC14.15, R35.8
RXD8: IC14.54, R34.8
RXD9: IC14.52, R34.5
RXD10: IC20.15, R49.8
RXD11: IC20.54, R48.8
RXD12: IC20.52, R48.5
RXD13: IC26.15, R63.8
RXD14: IC26.54, R62.8
RXD15: IC26.52, R62.5
RXD16: IC32.15, R77.8
RXD17: IC32.54, R76.8
RXD18: IC32.52, R76.5
SCL: IC1.29, IC2.8, IC3.1, IC4.23, R13.2, TEST2.1
SCL1: IC7.23, IC8.29, IC9.8, IC12.1, R15.2, TEST5.1
SCL2: IC13.23, IC14.29, IC15.8, IC18.1, R29.2, TEST9.1
SCL3: IC19.23, IC20.29, IC21.8, IC24.1, R43.2, TEST13.1
SCL4: IC25.23, IC26.29, IC27.8, IC30.1, R57.2, TEST17.1
SCL5: IC31.23, IC32.29, IC33.8, IC36.1, R71.2, TEST21.1
SDA: IC1.30, IC2.7, IC3.16, IC4.24, R14.2, TEST1.1
SDA1: IC7.24, IC8.30, IC9.7, IC12.16, R16.2, TEST6.1
SDA2: IC13.24, IC14.30, IC15.7, IC18.16, R30.2, TEST10.1
SDA3: IC19.24, IC20.30, IC21.7, IC24.16, R44.2, TEST14.1
SDA4: IC25.24, IC26.30, IC27.7, IC30.16, R58.2, TEST18.1
SDA5: IC31.24, IC32.30, IC33.7, IC36.16, R72.2, TEST22.1
SWCLK: IC1.49, SWD.1
SWCLK1: IC8.49, SWD1.1
SWCLK2: IC14.49, SWD2.1
SWCLK3: IC20.49, SWD3.1
SWCLK4: IC26.49, SWD4.1
SWCLK5: IC32.49, SWD5.1
SWDIO: IC1.46, SWD.2
SWDIO1: IC8.46, SWD1.2
SWDIO2: IC14.46, SWD2.2
SWDIO3: IC20.46, SWD3.2
SWDIO4: IC26.46, SWD4.2
SWDIO5: IC32.46, SWD5.2
TXD1: IC8.14, R21.7
TXD2: IC8.51, R20.6
TXD3: IC1.51, R5.6
TXD4: IC1.14, R4.7
TXD5: IC1.53, R5.7
TXD6: IC8.53, R20.7
TXD7: IC14.14, R35.7
TXD8: IC14.51, R34.6
TXD9: IC14.53, R34.7
TXD10: IC20.14, R49.7
TXD11: IC20.51, R48.6
TXD12: IC20.53, R48.7
TXD13: IC26.14, R63.7
TXD14: IC26.51, R62.6
TXD15: IC26.53, R62.7
TXD16: IC32.14, R77.7
TXD17: IC32.51, R76.6
TXD18: IC32.53, R76.7
VCC: D2.2, L2.1, R10.2, USB1.1
VCC1: D11.2, L6.1, R25.2, USB2.1
VCC2: D19.2, L9.1, R39.2, USB3.1
VCC3: D27.2, L12.1, R53.2, USB4.1
VCC4: D35.2, L15.1, R67.2, USB5.1
VCC5: D43.2, L18.1, R81.2, USB6.1
VCCA: C2.1, C13.1, C14.1, C15.1, IC2.1, IC2.2, IC3.2, IC3.4, IC3.6, IC3.13, IC4.8, IC4.9, IC4.13, L1.2
VCCA1: C16.1, C35.1, C42.1, C48.1, IC7.8, IC7.9, IC7.13, IC9.1, IC9.2, IC12.2, IC12.4, IC12.6, IC12.13, L4.2
VCCA2: C49.1, C59.1, C66.1, C72.1, IC13.8, IC13.9, IC13.13, IC15.1, IC15.2, IC18.2, IC18.4, IC18.6, IC18.13, L7.2
VCCA3: C73.1, C83.1, C90.1, C96.1, IC19.8, IC19.9, IC19.13, IC21.1, IC21.2, IC24.2, IC24.4, IC24.6, IC24.13, L10.2
VCCA4: C97.1, C107.1, C114.1, C120.1, IC25.8, IC25.9, IC25.13, IC27.1, IC27.2, IC30.2, IC30.4, IC30.6, IC30.13, L13.2
VCCA5: C121.1, C131.1, C138.1, C144.1, IC31.8, IC31.9, IC31.13, IC33.1, IC33.2, IC36.2, IC36.4, IC36.6, IC36.13, L16.2
VCC_PANEL: E$7.B10, E$7.B11
V_RC: C1.1, D1.3, IC6.1, IC6.3
V_RC1: C33.1, D16.3, IC11.1, IC11.3
V_RC2: C57.1, D24.3, IC17.1, IC17.3
V_RC3: C81.1, D32.3, IC23.1, IC23.3
V_RC4: C105.1, D40.3, IC29.1, IC29.3
V_RC5: C129.1, D48.3, IC35.1, IC35.3

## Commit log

2019-04-23 Designs
